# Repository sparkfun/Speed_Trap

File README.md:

SparkFun Speed Trap
=======

This is a project demonstrating how to display instantaneous speed from a LIDAR on two [large 7-segment displays](https://www.sparkfun.com/products/8530).

*Note the handprints on the wall...*

The new [LIDAR-Lite](https://www.sparkfun.com/products/13167) from PulsedLight is pretty nice. It outputs readings very quickly. From multiple distance readings we can calculate speed (velocity is the derivative of position).

Repository Contents
-------------------

* **/firmware** - The code that runs on the Arduino
* **/hardware** - An Arduino shield to easily connect a computer PSU and the 6 wires for the large digit driver backpack

License Information
-------------------

This design is [OSHW](http://www.oshwa.org/definition/) and public domain but you buy me a beer if you use this and we meet someday ([Beerware license](http://en.wikipedia.org/wiki/Beerware)).

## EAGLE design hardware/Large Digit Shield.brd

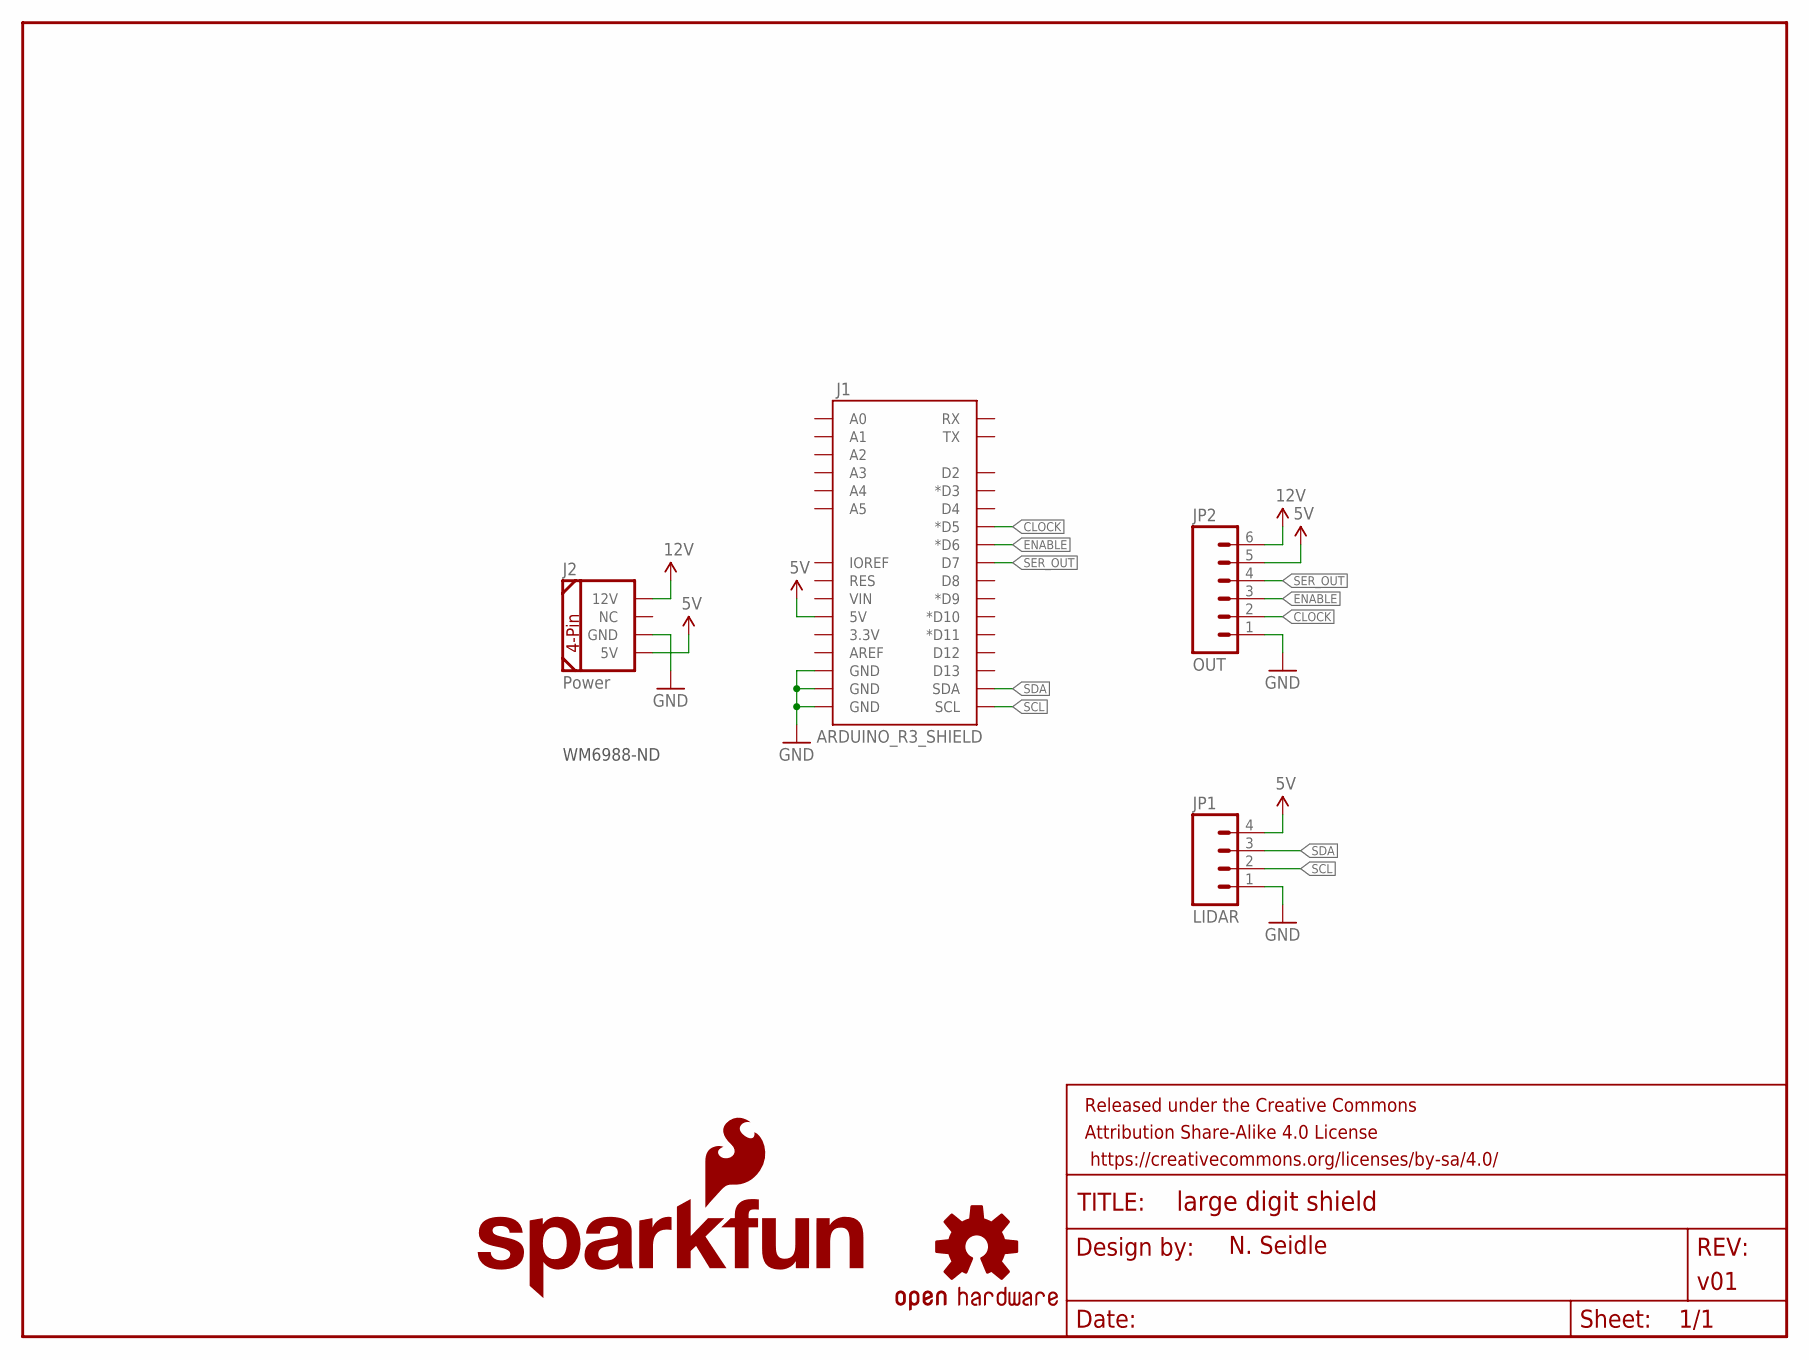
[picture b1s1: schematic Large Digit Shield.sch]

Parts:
FRAME1: FRAME-LETTER; CREATIVE_COMMONS
J1: ARDUINO_R3_SHIELD; UNO_R3_SHIELD
J2: Power; COMPUTER-PERIPHERAL-POWER-RA
JP1: LIDAR; JST-4-PTH
JP2: OUT; 1X06
LOGO1: SFE_LOGO_NAME_FLAME.2_INCH; SFE_LOGO_NAME_FLAME_.2
LOGO2: OSHW-LOGOS; OSHW-LOGO-S

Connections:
5V: J1.5V, J2.5V, JP1.4, JP2.5
12V: J2.12V, JP2.6
CLOCK: J1.D5 (*D5), JP2.2
ENABLE: J1.D6 (*D6), JP2.3
GND: J1.GND@0 (GND), J1.GND@1 (GND), J1.GND@2 (GND), J2.GND, JP1.1, JP2.1
SCL: J1.SCL, JP1.2
SDA: J1.SDA, JP1.3
SER_OUT: J1.D7, JP2.4

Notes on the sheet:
WM6988-ND

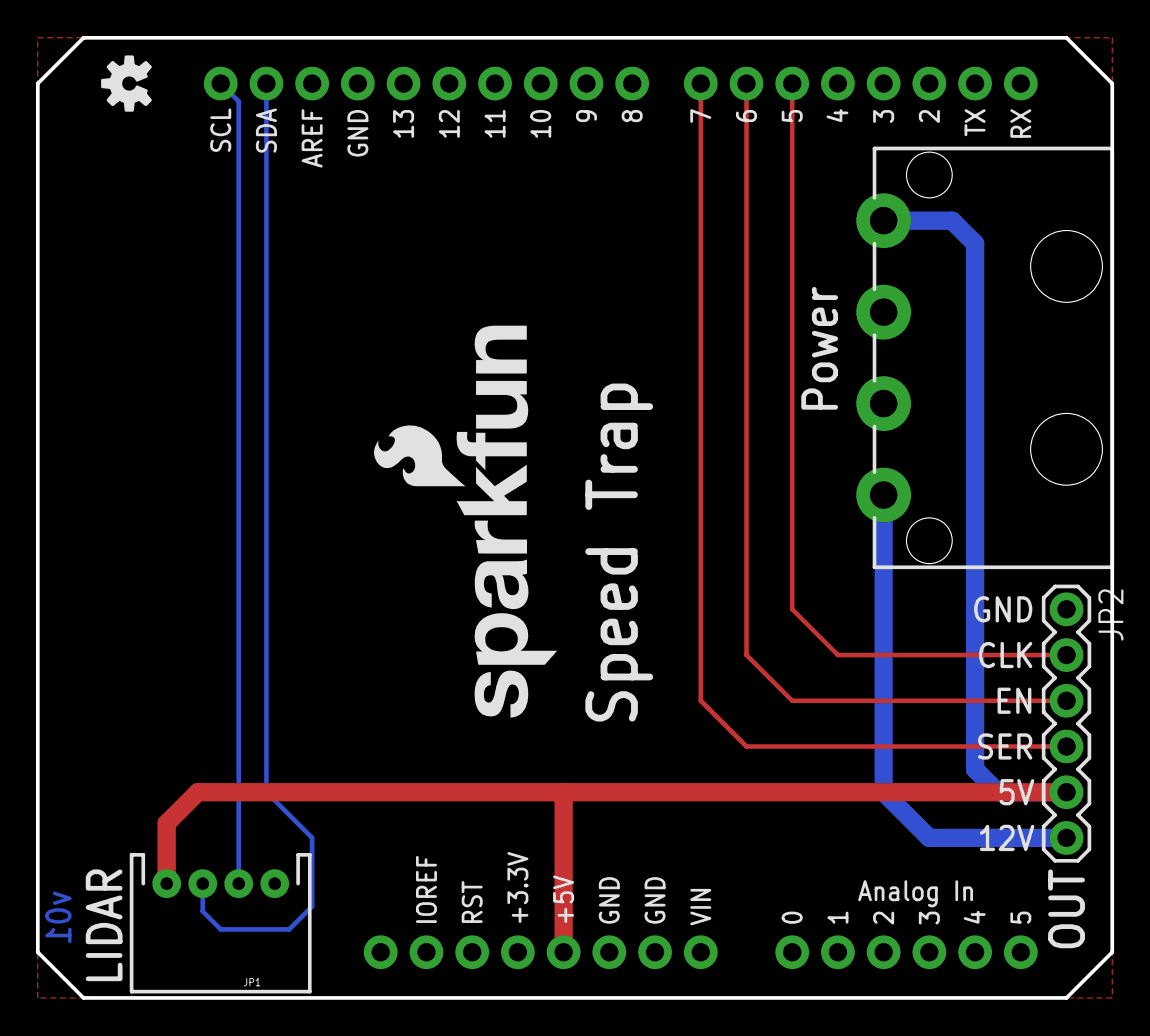
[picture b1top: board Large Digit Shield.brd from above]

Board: 2 copper layers, 59.7 x 53.3 mm, 7 parts (0 on the bottom side), 8 nets.

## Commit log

2015-06-17 :space_invader: Added .gitattributes & .gitignore files
2015-06-17 Update readme and adding image
2015-06-17 Readme fix
2015-08-18 Fixed small documentation issue A0->Enable
2022-07-02 Prevent writing beyond array length
    The current code creates a `deltas` array of `8` length, but the `deltaSpot` variable attempts to write at index `8` which causes various corruption. This changes so that it will only go to index `7`

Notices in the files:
parts and their libraries:
SparkFun-Aesthetics: Licensing: CC v3.0 Share-Alike You are welcome to use this library for commercial purposes.
SparkFun-Aesthetics: Released under the Creative Commons Attribution Share-Alike 4.0 License
SparkFun-Aesthetics: https://creativecommons.org/licenses/by-sa/4.0
